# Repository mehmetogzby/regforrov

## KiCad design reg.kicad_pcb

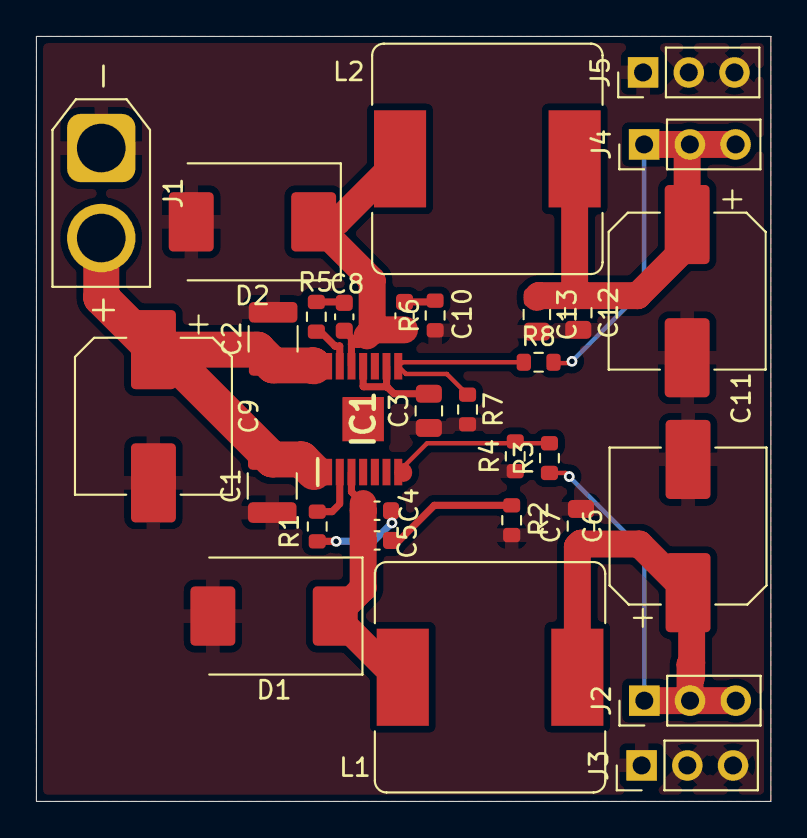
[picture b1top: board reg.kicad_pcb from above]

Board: 2 copper layers, 40.8 x 42.5 mm, 31 parts (0 on the bottom side), 15 nets.

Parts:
C1, C2: 10 µF; C_1210_3225Metric
C3: 4.7 µF; C_0805_2012Metric
C4, C8: 0.033 uF; C_0603_1608Metric
C5: 1000pF; C_0603_1608Metric
C6: 47uF; CP_Elec_8x10.5
C7, C12, C13: 10 µF; C_0805_2012Metric
C9, C11: 100uF; CP_Elec_8x10.5
C10: 1000 pF; C_0603_1608Metric
D1, D2: D_Schottky; D_SMC
IC1: TPS54383PWP; SOP65P640X120-15N
J1: Conn_01x02; AMASS_XT30U-M_1x02_P5.0mm_Vertical
J2, J3, J4, J5: Conn_01x03; PinHeader_1x03_P2.54mm_Vertical
L1: 47uH; L_Bourns_SRR1260
L2: 22uH; L_Bourns_SRR1260
R1, R5: 3.3Ω; R_0603_1608Metric
R2, R6: 10Ω; R_0603_1608Metric
R3: 51.1k; R_0603_1608Metric
R4: 3.65k; R_0603_1608Metric
R7: 3.83k; R_0603_1608Metric
R8: 20k; R_0603_1608Metric

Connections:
/+22.2v: C1.2, C2.1, C9.1, IC1.1 (PVDD1), IC1.14 (PVDD2), J1.2
GND: C1.1, C2.2, C3.1, C6.2, C7.2, C9.2, C11.2, C12.2, C13.2, D1.2 (A), D2.2 (A), IC1.4 (GND), IC1.5 (~EN1), IC1.6 (~EN2), IC1.15 (EP), J1.1, J3.1, J3.2, J3.3, J5.1, J5.2, J5.3, R2.1, R4.1, R6.1, R7.2
unnamed: C4.2, R1.1
unnamed: C5.1, R2.2
unnamed: C8.2, R5.1
unnamed: C10.1, R6.2
unnamed: C4.1, C5.2, D1.1 (K), IC1.3 (SW1), L1.2
unnamed: C8.1, C10.2, D2.1 (K), IC1.12 (SW2), L2.1
unnamed: IC1.2 (BOOT1), R1.2
unnamed: IC1.13 (BOOT2), R5.2
unnamed: C3.2, IC1.9 (ILIM2), IC1.11 (BP)
unnamed: IC1.7 (FB1), R3.2, R4.2
unnamed: IC1.8 (FB2), R7.1, R8.1
unnamed: C6.1, C7.1, J2.1, J2.2, J2.3, L1.1, R3.1
unnamed: C11.1, C12.1, C13.1, J4.1, J4.2, J4.3, L2.2, R8.2
